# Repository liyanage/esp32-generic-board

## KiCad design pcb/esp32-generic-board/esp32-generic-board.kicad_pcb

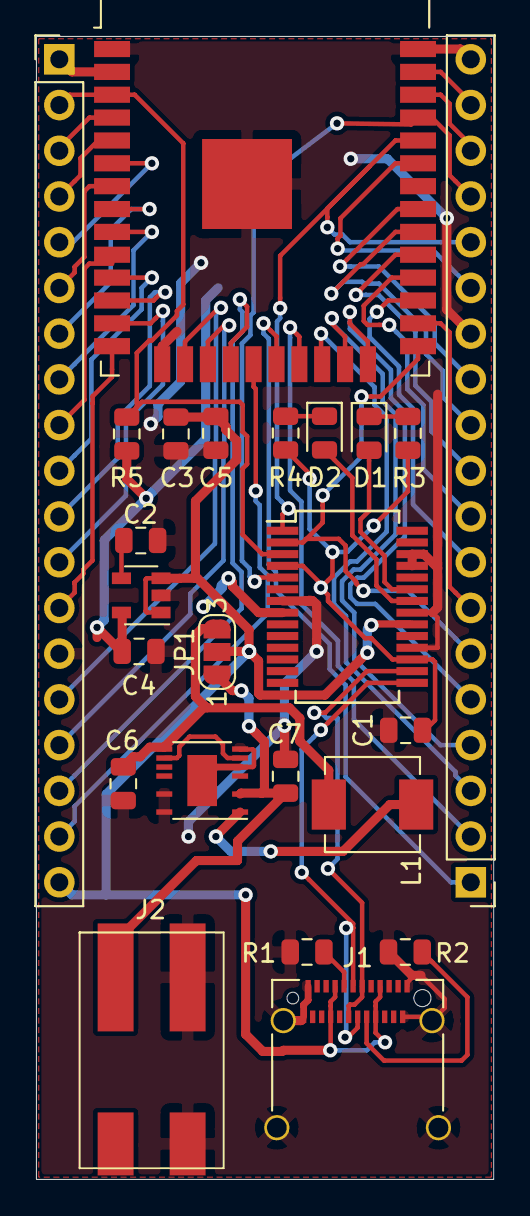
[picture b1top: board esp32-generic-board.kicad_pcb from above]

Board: 2 copper layers, 25.4 x 63.5 mm, 24 parts (0 on the bottom side), 50 nets.

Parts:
C1, C3: 100nF; C_0805_2012Metric
C2: 470pF; C_0805_2012Metric
C4: 2.2uF; C_0805_2012Metric
C5, C7: 4.7uF; C_0805_2012Metric
C6: 350uF; C_0805_2012Metric
D1, D2: LED; LED_0805_2012Metric
J1: USB_C_Receptacle; USB_C_Receptacle_Amphenol_12401610E4-2A_CircularHoles
J2: WAGO_2060-451_998-404
J3, J4: Conn_01x19; PinHeader_1x19_P2.54mm_Vertical
JP1: 5v_source; SolderJumper-3_P1.3mm_Open_RoundedPad1.0x1.5mm_NumberLabels
L1: 10uH; L_Vishay_IHLP-2020
R1, R2: 5.1k; R_0805_2012Metric
R3, R4: 270; R_0805_2012Metric
R5: 10k; R_0805_2012Metric
U1: MIC5219-3.3YM5; SOT-23-5
U2: LTC3630MSE; Linear_MSOP-12-16-1EP_3x4mm_P0.5mm
U3: FT232RL; SSOP-28_5.3x10.2mm_P0.65mm
U4: ESP32-WROOM-32

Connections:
/3v3: C4.1, J3.1, R5.1, U1.5, U4.2
/5v: C3.1, C5.1, J1.A4, J1.A9, J1.B4, J1.B9, J3.19, JP1.2, U1.1, U1.3, U3.20
/CC1: J1.A5, R1.2
/CC2: J1.B5, R2.2
/D+: J1.A7, J1.B7, U3.16
/D-: J1.A6, J1.B6, U3.15
/DTR-IO0: J4.6, U3.2, U4.25
/EN-RTS: J3.2, R5.2, U3.3, U4.3
/Vbuck: C6.1, JP1.3, L1.1, U2.9
/Vccio: C1.1, R3.1, R4.1, U3.4, U3.17
/Vext: C7.1, J2.2, JP1.1, U2.3
/rxled: D2.2, U3.22
/txled: D1.2, U3.23
GND: C1.2, C2.2, C3.2, C4.2, C5.2, C6.2, C7.2, J1.A1, J1.A12, J1.B1, J1.B12, J1.S1, J2.1, J3.14, J4.13, J4.19, R1.1, R2.1, U1.2, U2.6, U2.8, U2.14, U2.16, U2.17, U3.7, U3.18, U3.21, U3.25, U3.26, U4.1, U4.15, U4.38, U4.39
unnamed: C2.1, U1.4
unnamed: D1.1, R3.2
unnamed: D2.1, R4.2
unnamed: J3.3, U4.4
unnamed: J3.4, U4.5
unnamed: J3.5, U4.6
unnamed: J3.6, U4.7
unnamed: J3.7, U4.8
unnamed: J3.8, U4.9
unnamed: J3.9, U4.10
unnamed: J3.10, U4.11
unnamed: J3.11, U4.12
unnamed: J3.12, U4.13
unnamed: J3.13, U4.14
unnamed: J3.15, U4.16
unnamed: J3.16, U4.17
unnamed: J3.17, U4.18
unnamed: J3.18, U4.19
unnamed: J4.1, U4.20
unnamed: J4.2, U4.21
unnamed: J4.3, U4.22
unnamed: J4.4, U4.23
unnamed: J4.5, U4.24
unnamed: J4.7, U4.26
unnamed: J4.8, U4.27
unnamed: J4.9, U4.28
unnamed: J4.10, U4.29
unnamed: J4.11, U4.30
unnamed: J4.12, U4.31
unnamed: J4.14, U4.33
unnamed: J4.15, U3.1, U4.34
unnamed: J4.16, U3.5, U4.35
unnamed: J4.17, U4.36
unnamed: J4.18, U4.37
unnamed: L1.2, U2.1
unnamed: U2.7, U2.10

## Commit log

2019-11-05 init
2019-11-11 Version 2 with switch from FTDI to WCH CH340C USB-UART IC
